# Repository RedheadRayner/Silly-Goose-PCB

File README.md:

# Silly Goose

Silly Goose is the name of the first version of my handheld gaming PCB. I created this with the intention of having my own portable tetris gaming device. I am a great fan of tetris and was disappointed that most portable devices did not have the correct tetris rules or failed to save scores when powered off (so I took matters into my own hands!).

## Games

Currently, the following games are created:
- [Tetris](https://github.com/RedheadRayner/Tetris)

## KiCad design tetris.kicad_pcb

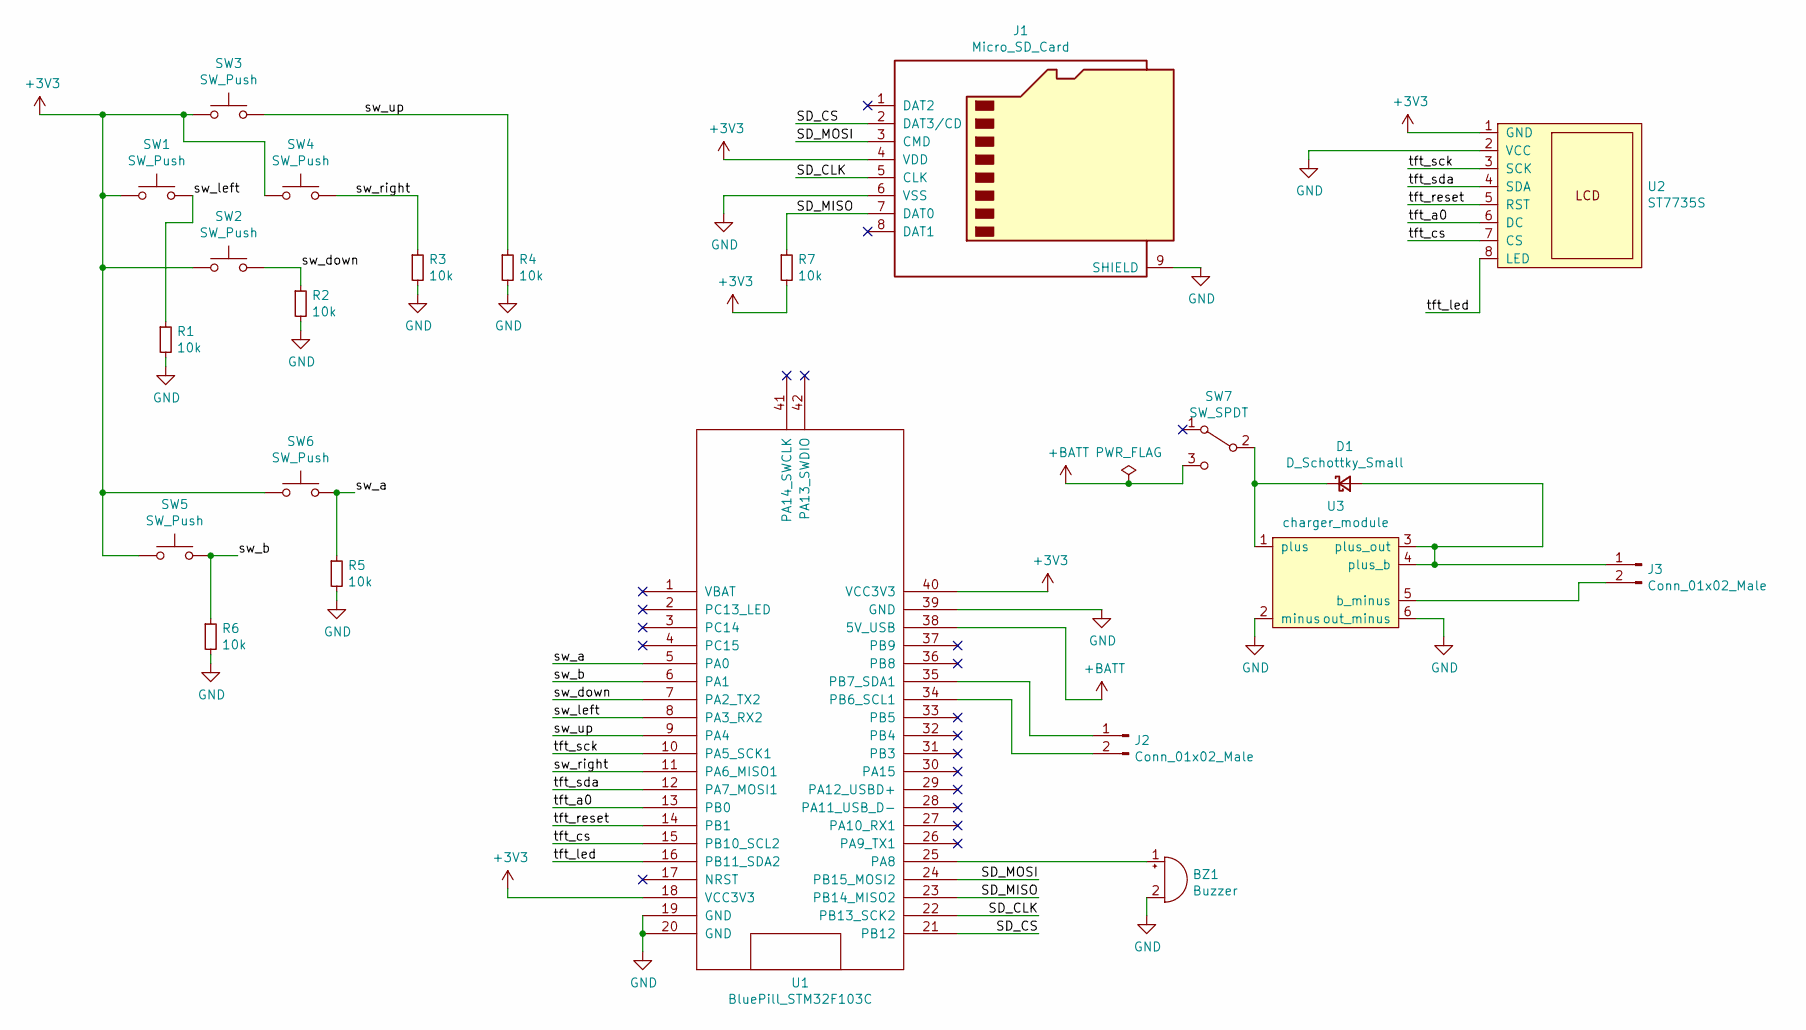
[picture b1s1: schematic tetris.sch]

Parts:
BZ1: Buzzer; Buzzer_CUI_CPT-9019S-SMT
D1: D_Schottky_Small; D_T-1_P5.08mm_Horizontal
J1: Micro_SD_Card; microSD_HC_Hirose_DM3AT-SF-PEJM5
J2: Conn_01x02_Male; PinHeader_1x02_P2.54mm_Horizontal
J3: Conn_01x02_Male; TestPoint_2Pads_Pitch5.08mm_Drill1.3mm
R1, R2, R3, R4, R5, R6, R7: 10k; R_Axial_DIN0207_L6.3mm_D2.5mm_P7.62mm_Horizontal
SW1, SW2, SW3, SW4, SW5, SW6: SW_Push; SW_PUSH_6mm
SW7: SW_SPDT; SW_SPDT_PCM12
U1: BluePill_STM32F103C
U2: ST7735S; st7735s
U3: charger_module

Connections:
+3V3: J1.4 (VDD), R7.2, SW1.1, SW2.1, SW3.1, SW4.1, SW5.1, SW6.1, U1.18 (VCC3V3), U1.40 (VCC3V3), U2.1 (GND)
+BATT: SW7.3 (C), U1.38 (5V_USB)
/SD_CLK: J1.5 (CLK), U1.22 (PB13_SCK2)
/SD_CS: J1.2 (DAT3/CD), U1.21 (PB12)
/SD_MISO: J1.7 (DAT0), R7.1, U1.23 (PB14_MISO2)
/SD_MOSI: J1.3 (CMD), U1.24 (PB15_MOSI2)
/sw_a: R5.1, SW6.2, U1.5 (PA0)
/sw_b: R6.1, SW5.2, U1.6 (PA1)
/sw_down: R2.1, SW2.2, U1.7 (PA2_TX2)
/sw_left: R1.1, SW1.2, U1.8 (PA3_RX2)
/sw_right: R3.1, SW4.2, U1.11 (PA6_MISO1)
/sw_up: R4.1, SW3.2, U1.9 (PA4)
/tft_a0: U1.13 (PB0), U2.6 (DC)
/tft_cs: U1.15 (PB10_SCL2), U2.7 (CS)
/tft_led: U1.16 (PB11_SDA2), U2.8 (LED)
/tft_reset: U1.14 (PB1), U2.5 (RST)
/tft_sck: U1.10 (PA5_SCK1), U2.3 (SCK)
/tft_sda: U1.12 (PA7_MOSI1), U2.4 (SDA)
GND: BZ1.2 (+), J1.6 (VSS), J1.9 (SHIELD), R1.2, R2.2, R3.2, R4.2, R5.2, R6.2, U1.19 (GND), U1.20 (GND), U1.39 (GND), U2.2 (VCC), U3.2 (minus), U3.6 (out_minus)
unnamed: BZ1.1 (-), U1.25 (PA8)
unnamed: D1.1 (K), SW7.2 (B), U3.1 (plus)
unnamed: D1.2 (A), J3.1, U3.3 (plus_out), U3.4 (plus_b)
unnamed: J2.1, U1.35 (PB7_SDA1)
unnamed: J2.2, U1.34 (PB6_SCL1)
unnamed: J3.2, U3.5 (b_minus)

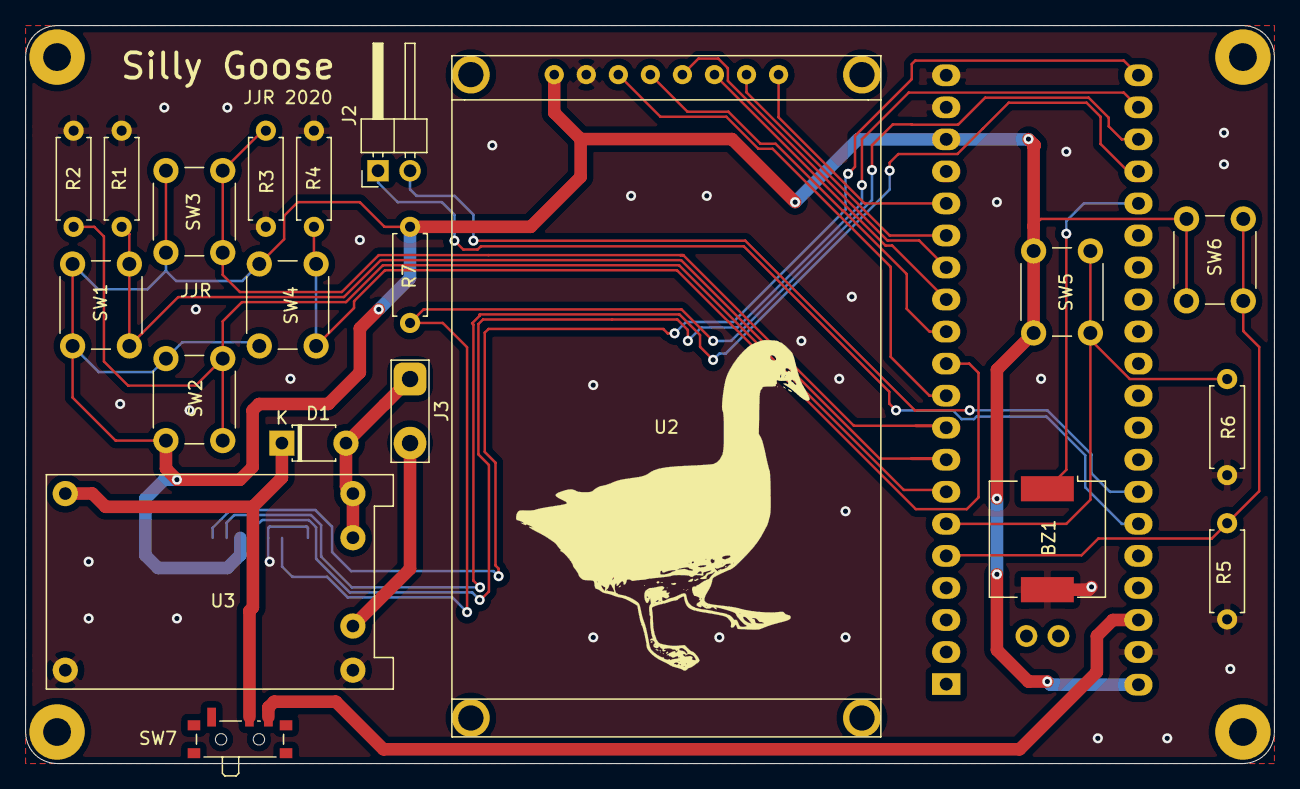
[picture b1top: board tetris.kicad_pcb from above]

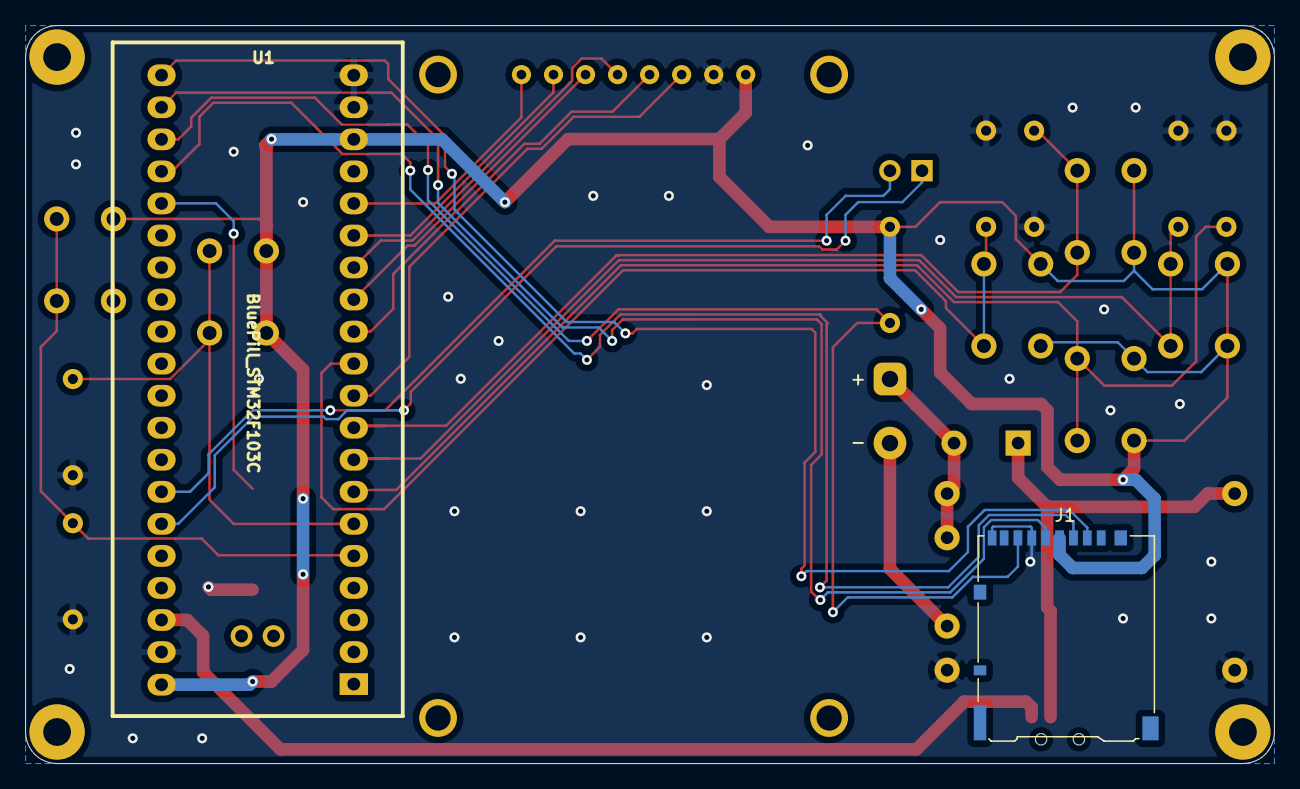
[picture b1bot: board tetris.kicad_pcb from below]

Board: 2 copper layers, 99.0 x 58.5 mm, 26 parts (2 on the bottom side), 25 nets.

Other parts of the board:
 : MountingHole_2.2mm_M2_Pad
 #2,  #3,  #4: MountingHole_2.2mm_M2_Pad

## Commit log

2020-09-04 uploading kicad project
